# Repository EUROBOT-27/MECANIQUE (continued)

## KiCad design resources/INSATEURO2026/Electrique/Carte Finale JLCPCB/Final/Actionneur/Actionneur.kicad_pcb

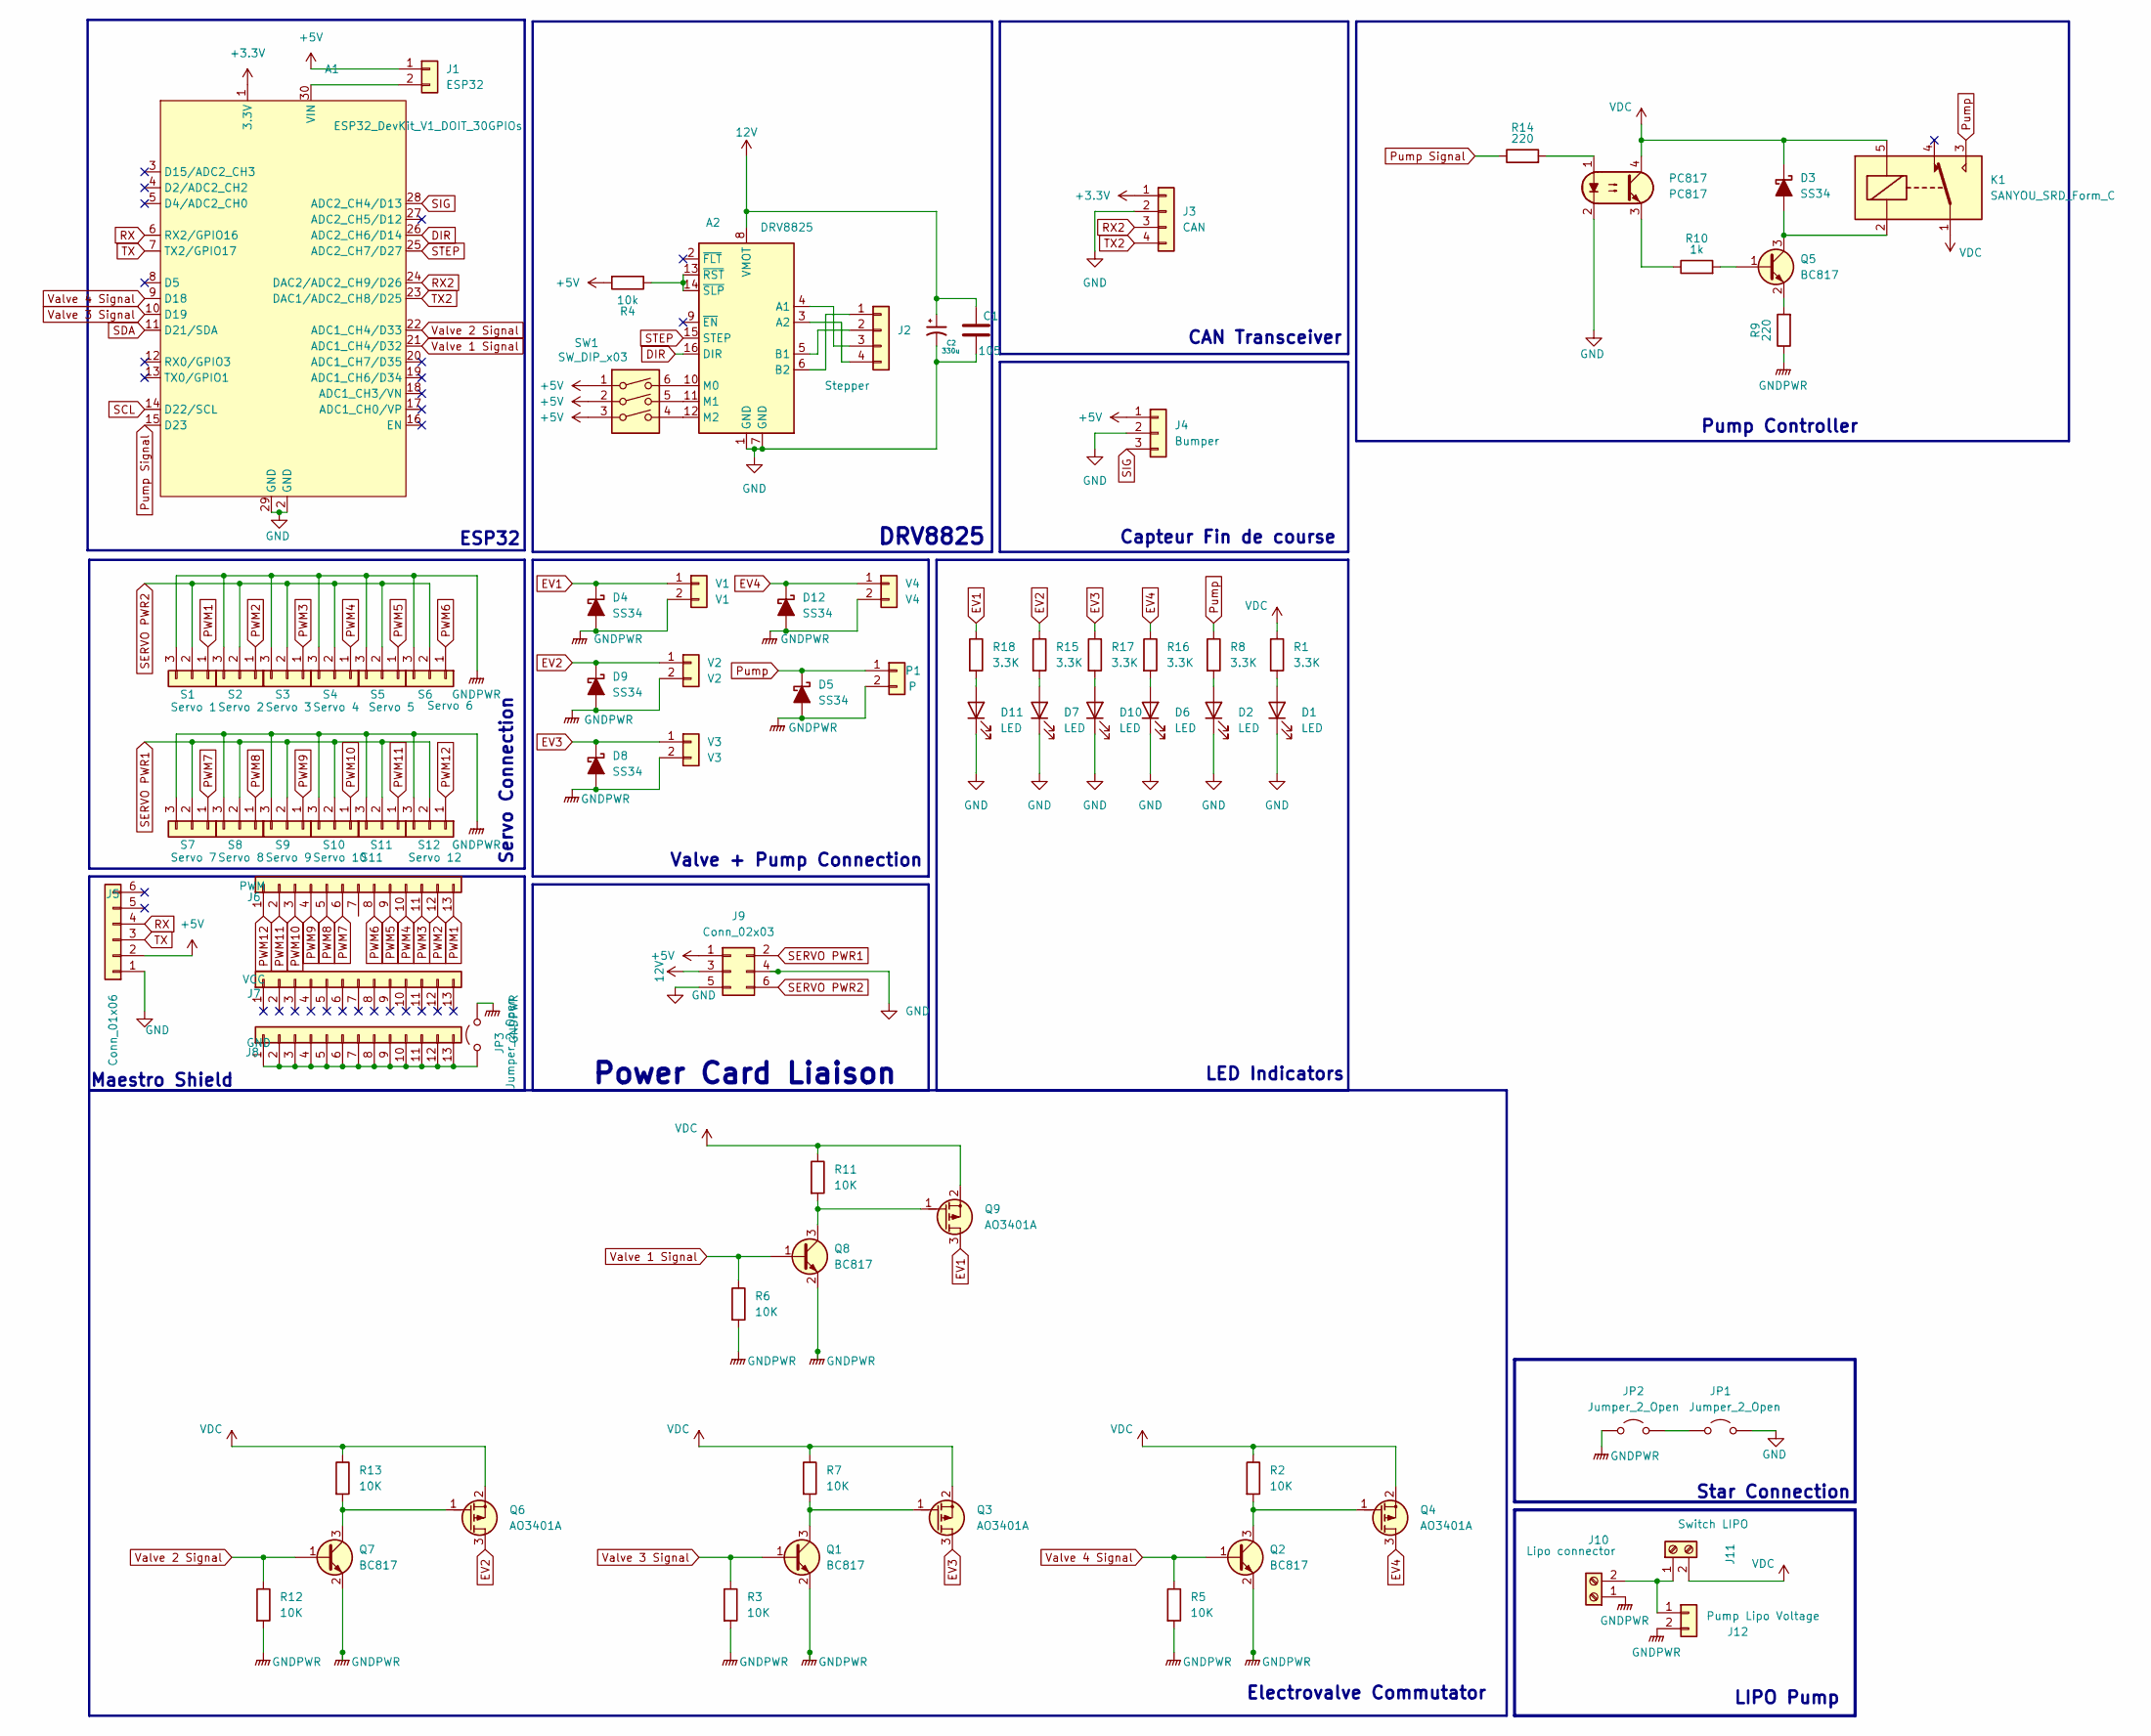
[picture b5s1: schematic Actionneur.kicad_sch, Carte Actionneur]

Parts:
A1: ESP32_DevKit_V1_DOIT_30GPIOs; DOIT_ESP32_DEVKIT_30Pins
A2: DRV8825; Pololu_Breakout-16_15.2x20.3mm
C1: 105; C_0603_1608Metric
C2: 330u; CP_Elec_10x10.5
D1, D2, D6, D7, D10, D11: LED; LED_0603_1608Metric
D3, D4, D5, D8, D9, D12: SS34; D_SOD-323
J1: ESP32; JST_XH_B2B-XH-A_1x02_P2.50mm_Vertical
J2: Stepper; JST_EH_B4B-EH-A_1x04_P2.50mm_Vertical
J3: CAN; JST_EH_B4B-EH-A_1x04_P2.50mm_Vertical
J4: Bumper; JST_EH_B3B-EH-A_1x03_P2.50mm_Vertical
J5: Conn_01x06; PinSocket_1x06_P2.54mm_Vertical
J6: PWM; PinSocket_1x13_P2.54mm_Vertical
J7: VCC; PinSocket_1x13_P2.54mm_Vertical
J8: GND; PinSocket_1x13_P2.54mm_Vertical
J9: Conn_02x03; Molex_Mini-Fit_Jr_5566-06A_2x03_P4.20mm_Vertical
J10: Lipo connector; TerminalBlock_Phoenix_MKDS-1,5-2-5.08_1x02_P5.08mm_Horizont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
J11: Switch LIPO; TerminalBlock_Phoenix_MKDS-1,5-2-5.08_1x02_P5.08mm_Horizont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
J12: Pump Lipo Voltage; JST_PH_B2B-PH-K_1x02_P2.00mm_Vertical
JP1, JP3: Jumper_2_Open; TestPoint_2Pads_Pitch2.54mm_Drill0.8mm
JP2: Jumper_2_Open; Jumper_P2.54mm_D0.7mm
K1: SANYOU_SRD_Form_C; Relay_SPDT_SANYOU_SRD_Series_Form_C
P1: P; JST_PH_B2B-PH-K_1x02_P2.00mm_Vertical
PC817: PC817; DIP-4_W7.62mm
Q1, Q2, Q5, Q7, Q8: BC817; SOT-23
Q3, Q4, Q6, Q9: AO3401A; SOT-23
R1, R8, R15, R16, R17, R18: 3.3K; R_0603_1608Metric
R2, R3, R5, R6, R7, R11, R12, R13: 10K; R_0603_1608Metric
R4: 10k; R_0603_1608Metric
R9, R14: 220; R_0603_1608Metric
R10: 1k; R_0603_1608Metric
S1: Servo 1; PinHeader_1x03_P2.54mm_Vertical
S2: Servo 2; PinHeader_1x03_P2.54mm_Vertical
S3: Servo 3; PinHeader_1x03_P2.54mm_Vertical
S4: Servo 4; PinHeader_1x03_P2.54mm_Vertical
S5: Servo 5; PinHeader_1x03_P2.54mm_Vertical
S6: Servo 6; PinHeader_1x03_P2.54mm_Vertical
S7: Servo 7; PinHeader_1x03_P2.54mm_Vertical
S8: Servo 8; PinHeader_1x03_P2.54mm_Vertical
S9: Servo 9; PinHeader_1x03_P2.54mm_Vertical
S10: Servo 10; PinHeader_1x03_P2.54mm_Vertical
S11: S11; PinHeader_1x03_P2.54mm_Vertical
S12: Servo 12; PinHeader_1x03_P2.54mm_Vertical
SW1: SW_DIP_x03; SW_DIP_SPSTx03_Slide_6.7x9.18mm_W6.73mm_P2.54mm_LowProfile_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
V1: V1; JST_PH_B2B-PH-K_1x02_P2.00mm_Vertical
V2: V2; JST_PH_B2B-PH-K_1x02_P2.00mm_Vertical
V3: V3; JST_PH_B2B-PH-K_1x02_P2.00mm_Vertical
V4: V4; JST_PH_B2B-PH-K_1x02_P2.00mm_Vertical

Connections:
12V: A2.8 (VMOT), C1.1, C2.1, J9.3
+3.3V: A1.1 (3.3V), J3.1
+5V: J1.1, J4.1, J5.2, J9.1, R4.2, SW1.1, SW1.2, SW1.3
DIR: A1.26 (ADC2_CH6/D14), A2.16 (DIR)
EV1: D4.1 (K), Q9.3 (D), R18.1, V1.1
EV2: D9.1 (K), Q6.3 (D), R15.1, V2.1
EV3: D8.1 (K), Q3.3 (D), R17.1, V3.1
EV4: D12.1 (K), Q4.3 (D), R16.1, V4.1
GND: A1.2 (GND), A1.29 (GND), A2.1 (GND), A2.7 (GND), C1.2, C2.2, D1.1 (K), D2.1 (K), D6.1 (K), D7.1 (K), D10.1 (K), D11.1 (K), J3.2, J4.2, J5.1, J9.4, J9.5, JP1.2 (B), PC817.2
GNDPWR: D4.2 (A), D5.2 (A), D8.2 (A), D9.2 (A), D12.2 (A), J10.1, J12.2, JP2.1 (A), JP3.2 (B), P1.2, Q1.2 (E), Q2.2 (E), Q7.2 (E), Q8.2 (E), R3.2, R5.2, R6.2, R9.1, R12.2, S1.3, S2.3, S3.3, S4.3, S5.3, S6.3, S7.3, S8.3, S9.3, S10.3, S11.3, S12.3, V1.2, V2.2, V3.2, V4.2
unnamed: A1.30 (VIN), J1.2
unnamed: A2.4 (A1), J2.3
unnamed: A2.3 (A2), J2.4
unnamed: A2.5 (B1), J2.2
unnamed: A2.6 (B2), J2.1
unnamed: A2.10 (M0), SW1.6
unnamed: A2.11 (M1), SW1.5
unnamed: A2.12 (M2), SW1.4
unnamed: A2.13 (~RST), A2.14 (~SLP), R4.1
unnamed: D1.2 (A), R1.2
unnamed: D2.2 (A), R8.2
unnamed: D3.2 (A), K1.2, Q5.3 (C)
unnamed: D6.2 (A), R16.2
unnamed: D7.2 (A), R15.2
unnamed: D10.2 (A), R17.2
unnamed: D11.2 (A), R18.2
unnamed: J8.1, J8.2, J8.3, J8.4, J8.5, J8.6, J8.7, J8.8, J8.9, J8.10, J8.11, J8.12, J8.13, JP3.1 (A)
unnamed: J10.2, J11.1, J12.1
unnamed: JP1.1 (A), JP2.2 (B)
unnamed: PC817.1, R14.2
unnamed: PC817.3, R10.1
unnamed: Q1.3 (C), Q3.1 (G), R7.2
unnamed: Q2.3 (C), Q4.1 (G), R2.2
unnamed: Q5.1 (B), R10.2
unnamed: Q5.2 (E), R9.2
unnamed: Q6.1 (G), Q7.3 (C), R13.2
unnamed: Q8.3 (C), Q9.1 (G), R11.2
PWM1: J6.13, S1.1
PWM2: J6.12, S2.1
PWM3: J6.11, S3.1
PWM4: J6.10, S4.1
PWM5: J6.9, S5.1
PWM6: J6.8, S6.1
PWM7: J6.6, S7.1
PWM8: J6.5, S8.1
PWM9: J6.4, S9.1
PWM10: J6.3, S10.1
PWM11: J6.2, S11.1
PWM12: J6.1, S12.1
Pump: D5.1 (K), K1.3, P1.1, R8.1
Pump Signal: A1.15 (D23), R14.1
RX: A1.6 (RX2/GPIO16), J5.4
RX2: A1.24 (DAC2/ADC2_CH9/D26), J3.3
SCL: A1.14 (D22/SCL)
SDA: A1.11 (D21/SDA)
SERVO PWR1: J9.2, S7.2, S8.2, S9.2, S10.2, S11.2, S12.2
SERVO PWR2: J9.6, S1.2, S2.2, S3.2, S4.2, S5.2, S6.2
SIG: A1.28 (ADC2_CH4/D13), J4.3
STEP: A1.25 (ADC2_CH7/D27), A2.15 (STEP)
TX: A1.7 (TX2/GPIO17), J5.3
TX2: A1.23 (DAC1/ADC2_CH8/D25), J3.4
VDC: D3.1 (K), J11.2, K1.1, K1.5, PC817.4, Q3.2 (S), Q4.2 (S), Q6.2 (S), Q9.2 (S), R1.1, R2.1, R7.1, R11.1, R13.1
Valve 1 Signal: A1.21 (ADC1_CH4/D32), Q8.1 (B), R6.1
Valve 2 Signal: A1.22 (ADC1_CH4/D33), Q7.1 (B), R12.1
Valve 3 Signal: A1.10 (D19), Q1.1 (B), R3.1
Valve 4 Signal: A1.9 (D18), Q2.1 (B), R5.1

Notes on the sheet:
LED Indicators
ESP32
LIPO Pump
Valve + Pump Connection
Star Connection
CAN Transceiver
Maestro Shield
Electrovalve Commutator
DRV8825
Pump Controller
Power Card Liaison
Servo Connection
Capteur Fin de course

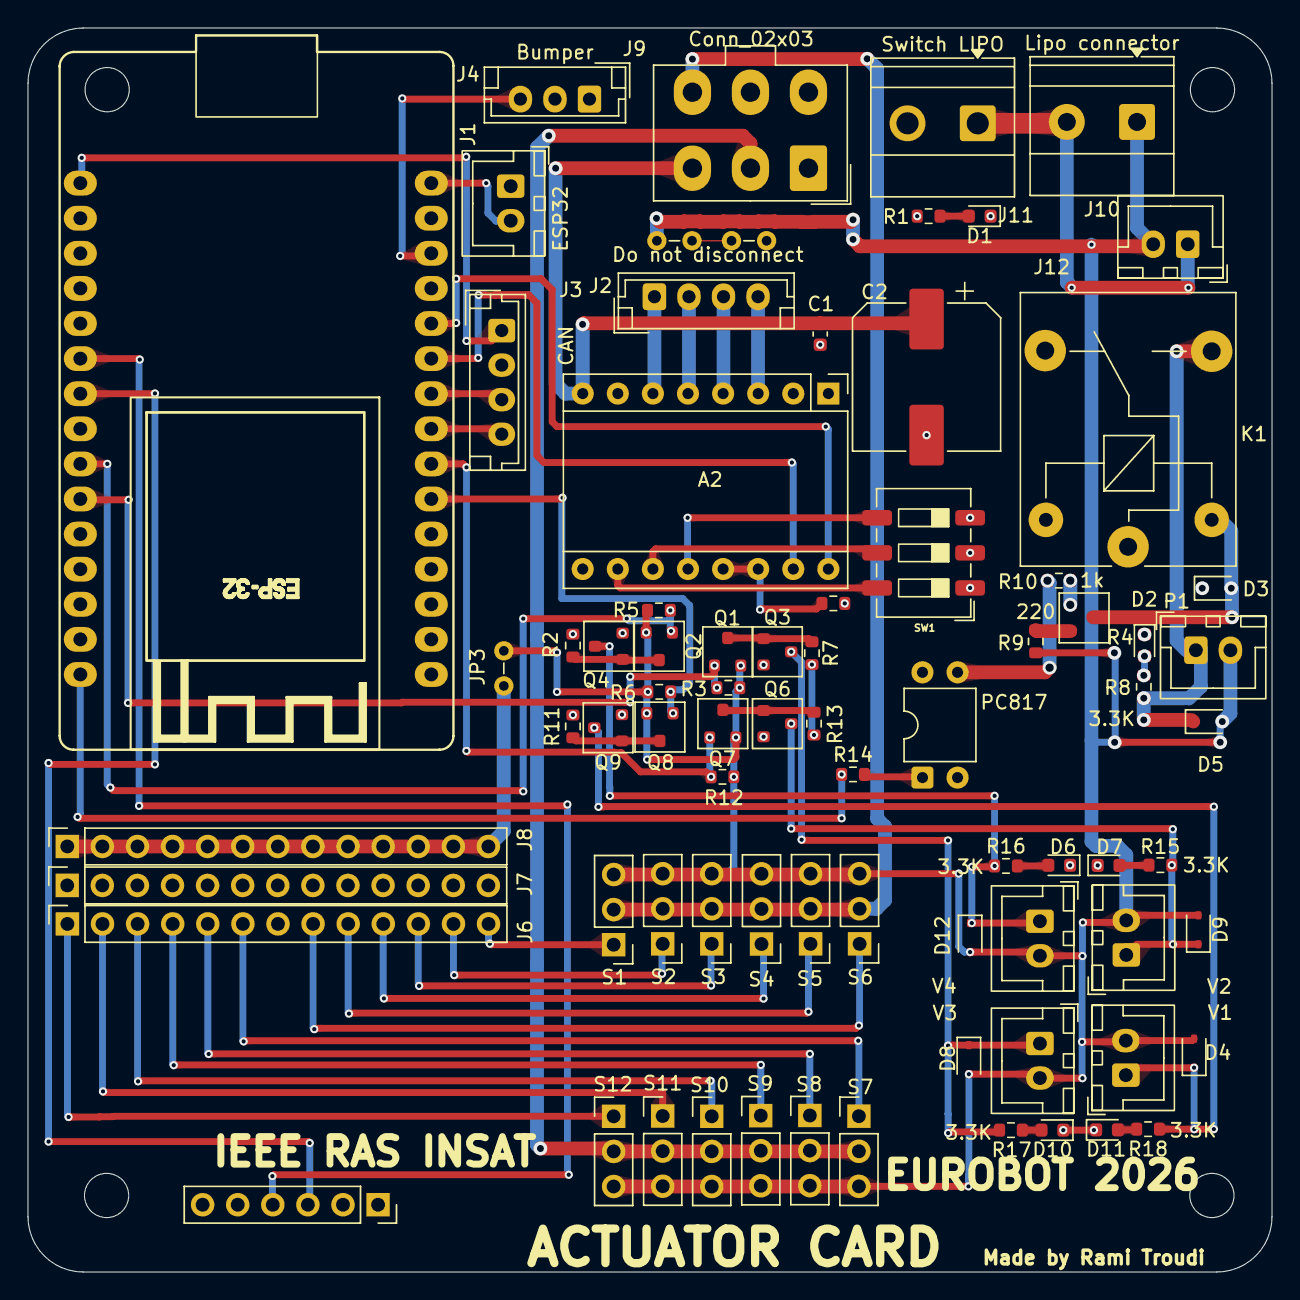
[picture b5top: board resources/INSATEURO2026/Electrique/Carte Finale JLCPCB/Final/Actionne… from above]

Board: 4 copper layers, 90.0 x 90.0 mm, 78 parts (0 on the bottom side), 64 nets.

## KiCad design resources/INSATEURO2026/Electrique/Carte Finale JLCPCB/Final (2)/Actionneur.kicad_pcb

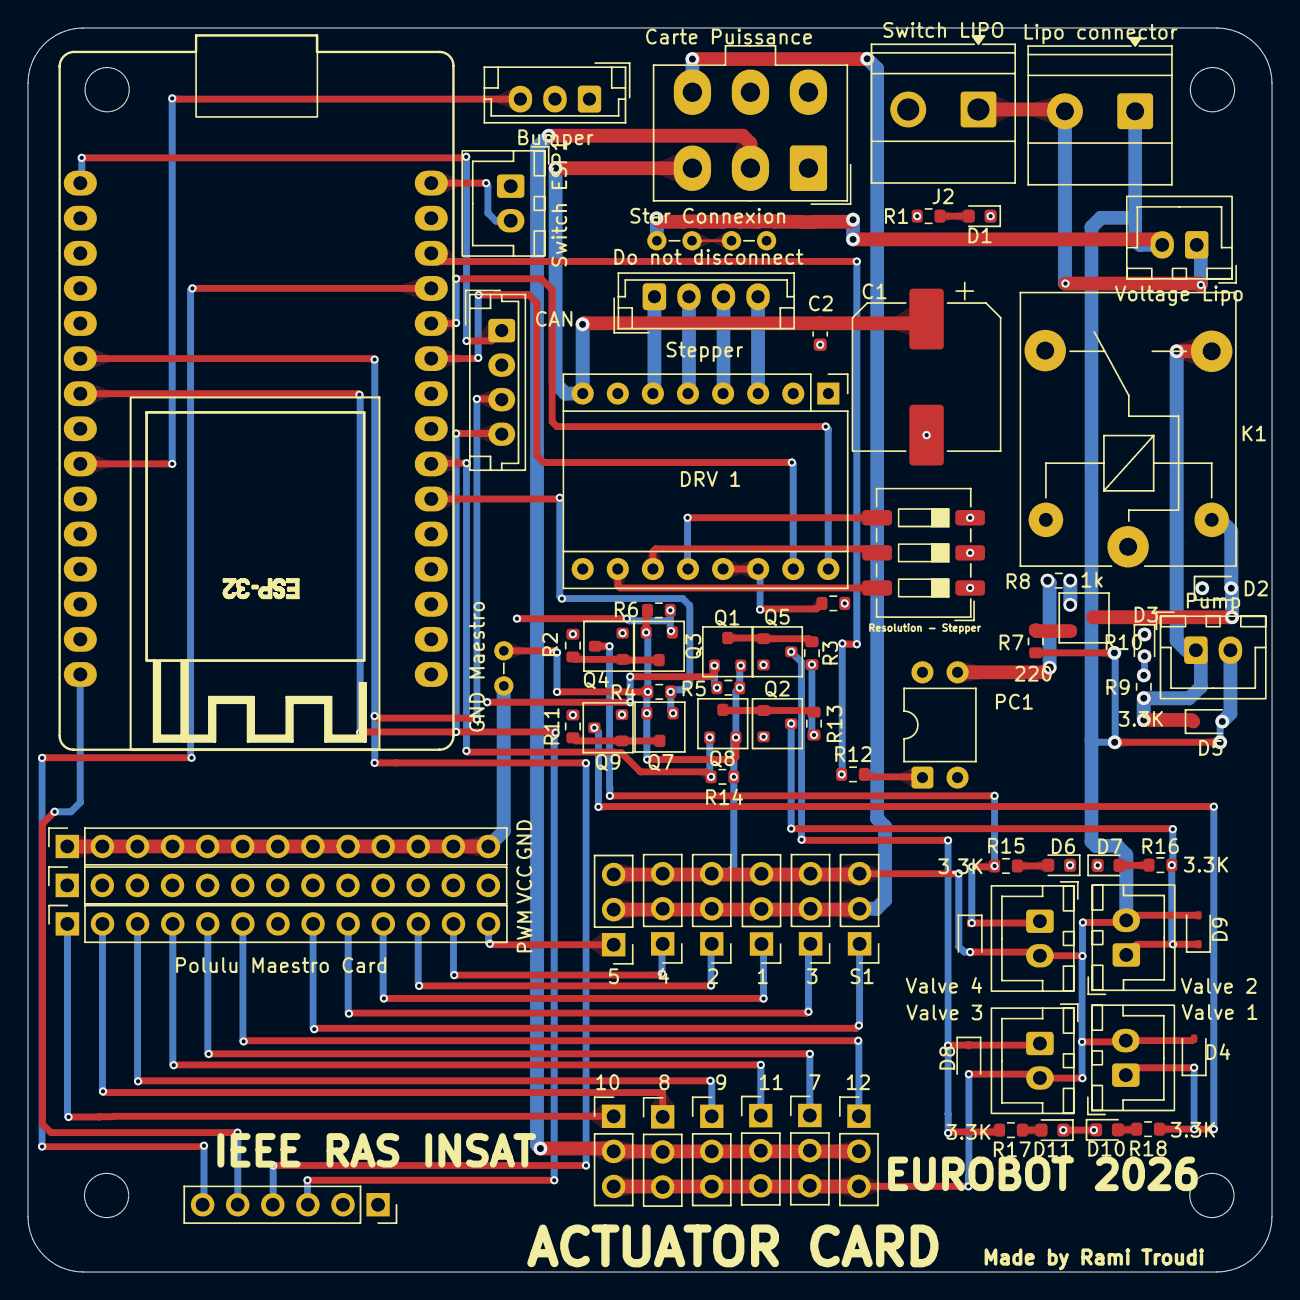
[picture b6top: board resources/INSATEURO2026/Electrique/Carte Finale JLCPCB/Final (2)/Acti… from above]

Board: 4 copper layers, 90.0 x 90.0 mm, 78 parts (0 on the bottom side), 64 nets.

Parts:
1: Servo 12; PinHeader_1x03_P2.54mm_Vertical
2: Servo 9; PinHeader_1x03_P2.54mm_Vertical
3: Servo 10; PinHeader_1x03_P2.54mm_Vertical
4: Servo 8; PinHeader_1x03_P2.54mm_Vertical
5: Servo 11; PinHeader_1x03_P2.54mm_Vertical
7: Servo 3; PinHeader_1x03_P2.54mm_Vertical
8: Servo 5; PinHeader_1x03_P2.54mm_Vertical
9: Servo 6; PinHeader_1x03_P2.54mm_Vertical
10: Servo 1; PinHeader_1x03_P2.54mm_Vertical
11: Servo 2; PinHeader_1x03_P2.54mm_Vertical
12: Servo 4; PinHeader_1x03_P2.54mm_Vertical
A1: ESP32_DevKit_V1_DOIT_30GPIOs; DOIT_ESP32_DEVKIT_30Pins
Bumper: Conn_01x03; JST_EH_B3B-EH-A_1x03_P2.50mm_Vertical
C1: 1000u; CP_Elec_10x10.5
C2: 105; C_0603_1608Metric
CAN: Conn_01x04; JST_EH_B4B-EH-A_1x04_P2.50mm_Vertical
Carte Puissance: Conn_02x03; Molex_Mini-Fit_Jr_5566-06A_2x03_P4.20mm_Vertical
D1, D3, D6, D7, D10, D11: LED; LED_0603_1608Metric
D2, D4, D5, D8, D9: SS34; D_SOD-323
DRV 1: Pololu_Breakout_DRV8825; Pololu_Breakout-16_15.2x20.3mm
GND: GND; PinSocket_1x13_P2.54mm_Vertical
GND Maestro: Jumper_2_Open; Jumper_P2.54mm_D0.7mm
J1: Lipo connector; TerminalBlock_Phoenix_MKDS-1,5-2-5.08_1x02_P5.08mm_Horizont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
J2: Switch LIPO; TerminalBlock_Phoenix_MKDS-1,5-2-5.08_1x02_P5.08mm_Horizont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
J3: Conn_01x06; PinSocket_1x06_P2.54mm_Vertical
JP1: Jumper_2_Open; Jumper_P2.54mm_D0.7mm
K1: SANYOU_SRD_Form_C; Relay_SPDT_SANYOU_SRD_Series_Form_C
PC1: PC817; DIP-4_W7.62mm
PWM: PWM; PinSocket_1x13_P2.54mm_Vertical
Polulu Maestro Card: SS34; D_SOD-323
Pump: V1; JST_XH_B2B-XH-A_1x02_P2.50mm_Vertical
Q1, Q3, Q6, Q7, Q8: BC817; SOT-23
Q2, Q4, Q5, Q9: AO3401A; SOT-23
R1, R9, R15, R16, R17, R18: 3.3K; R_0603_1608Metric
R2, R3, R4, R5, R6, R11, R13, R14: 10K; R_0603_1608Metric
R7, R12: 220; R_0603_1608Metric
R8: 1k; R_0603_1608Metric
R10: 10k; R_0603_1608Metric
Resolution - Stepper: SW_DIP_x03; SW_DIP_SPSTx03_Slide_6.7x9.18mm_W6.73mm_P2.54mm_LowProfile_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
S1: Servo 1; PinHeader_1x03_P2.54mm_Vertical
Star Connexion: Jumper_2_Open; Jumper_P2.54mm_D0.7mm
Stepper: Stepper connector; JST_EH_B4B-EH-A_1x04_P2.50mm_Vertical
Switch ESP1: V1; JST_XH_B2B-XH-A_1x02_P2.50mm_Vertical
VCC: VCC; PinSocket_1x13_P2.54mm_Vertical
Valve 1, Valve 2, Valve 3, Valve 4: V1; JST_XH_B2B-XH-A_1x02_P2.50mm_Vertical
Voltage Lipo: Pump Lipo Voltage; JST_XH_B2B-XH-A_1x02_P2.50mm_Vertical

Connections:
12V: C1.1, C2.1, Carte Puissance.3, DRV 1.8 (VMOT)
+3.3V: A1.1 (3.3V), CAN.1
+5V: Bumper.1, Carte Puissance.1, J3.2, R10.2, Resolution - Stepper.1, Resolution - Stepper.2, Resolution - Stepper.3
DIR: A1.26 (ADC2_CH6/D14), DRV 1.16 (DIR)
ERR: A1.27 (ADC2_CH5/D12), J3.6
EV1: D4.1 (K), Q9.3 (D), R18.1, Valve 1.1
EV2: D9.1 (K), Q2.3 (D), R16.1, Valve 2.1
EV3: D8.1 (K), Q5.3 (D), R17.1, Valve 3.1
EV4: Polulu Maestro Card.1 (K), Q4.3 (D), R15.1, Valve 4.1
GND: A1.2 (GND), A1.29 (GND), Bumper.2, C1.2, C2.2, CAN.2, Carte Puissance.4, Carte Puissance.5, D1.1 (K), D3.1 (K), D6.1 (K), D7.1 (K), D10.1 (K), D11.1 (K), DRV 1.1 (GND), DRV 1.7 (GND), J3.1, PC1.2, Star Connexion.2 (B)
GNDPWR: 1.3, 2.3, 3.3, 4.3, 5.3, 7.3, 8.3, 9.3, 10.3, 11.3, 12.3, D4.2 (A), D5.2 (A), D8.2 (A), D9.2 (A), GND Maestro.2 (B), J1.1, JP1.1 (A), Polulu Maestro Card.2 (A), Pump.2, Q1.2 (E), Q3.2 (E), Q7.2 (E), Q8.2 (E), R4.2, R5.2, R6.2, R7.1, R14.2, S1.3, Valve 1.2, Valve 2.2, Valve 3.2, Valve 4.2, Voltage Lipo.2
unnamed: A1.30 (VIN), Switch ESP1.2
unnamed: DRV 1.4 (A1), Stepper.3
unnamed: DRV 1.3 (A2), Stepper.4
unnamed: DRV 1.5 (B1), Stepper.2
unnamed: DRV 1.6 (B2), Stepper.1
unnamed: DRV 1.10 (M0), Resolution - Stepper.6
unnamed: DRV 1.11 (M1), Resolution - Stepper.5
unnamed: DRV 1.12 (M2), Resolution - Stepper.4
unnamed: DRV 1.13 (~RST), DRV 1.14 (~SLP), R10.1
unnamed: D2.2 (A), K1.2, Q6.3 (C)
unnamed: D10.2 (A), R18.2
unnamed: D7.2 (A), R16.2
unnamed: D11.2 (A), R17.2
unnamed: D6.2 (A), R15.2
unnamed: D3.2 (A), R9.2
unnamed: D1.2 (A), R1.2
unnamed: GND.1, GND.2, GND.3, GND.4, GND.5, GND.6, GND.7, GND.8, GND.9, GND.10, GND.11, GND.12, GND.13, GND Maestro.1 (A)
unnamed: J1.J27 (Pin_2), J2.1, Voltage Lipo.1
unnamed: JP1.2 (B), Star Connexion.1 (A)
unnamed: PC1.1, R12.2
unnamed: PC1.3, R8.1
unnamed: Q2.1 (G), Q8.3 (C), R13.2
unnamed: Q1.3 (C), Q5.1 (G), R3.2
unnamed: Q7.3 (C), Q9.1 (G), R11.2
unnamed: Q3.3 (C), Q4.1 (G), R2.2
unnamed: Q6.1 (B), R8.2
unnamed: Q6.2 (E), R7.2
PWM1: PWM.13, S1.1
PWM2: 4.1, PWM.12
PWM3: 2.1, PWM.11
PWM4: 3.1, PWM.10
PWM5: 5.1, PWM.9
PWM6: 1.1, PWM.8
PWM7: 10.1, PWM.6
PWM8: 11.1, PWM.5
PWM9: 7.1, PWM.4
PWM10: 12.1, PWM.3
PWM11: 8.1, PWM.2
PWM12: 9.1, PWM.1
Pump: D5.1 (K), K1.3, Pump.1, R9.1
Pump Signal: A1.28 (ADC2_CH4/D13), R12.1
RST: A1.15 (D23), J3.5
RX: A1.6 (RX2/GPIO16), CAN.3, J3.4
SERVO PWR1: 7.2, 8.2, 9.2, 10.2, 11.2, 12.2, Carte Puissance.2
SERVO PWR2: 1.2, 2.2, 3.2, 4.2, 5.2, Carte Puissance.6, S1.2
SIG: A1.9 (D18), Bumper.3
STEP: A1.25 (ADC2_CH7/D27), DRV 1.15 (STEP)
TX: A1.7 (TX2/GPIO17), CAN.4, J3.3
VDC: D2.1 (K), J2.2, K1.1, K1.5, PC1.4, Q2.2 (S), Q4.2 (S), Q5.2 (S), Q9.2 (S), R1.1, R2.1, R3.1, R11.1, R13.1
Valve 1 Signal: A1.21 (ADC1_CH4/D32), Q7.1 (B), R4.1
Valve 2 Signal: A1.22 (ADC1_CH4/D33), Q8.1 (B), R14.1
Valve 3 Signal: A1.23 (DAC1/ADC2_CH8/D25), Q1.1 (B), R5.1
Valve 4 Signal: A1.24 (DAC2/ADC2_CH9/D26), Q3.1 (B), R6.1

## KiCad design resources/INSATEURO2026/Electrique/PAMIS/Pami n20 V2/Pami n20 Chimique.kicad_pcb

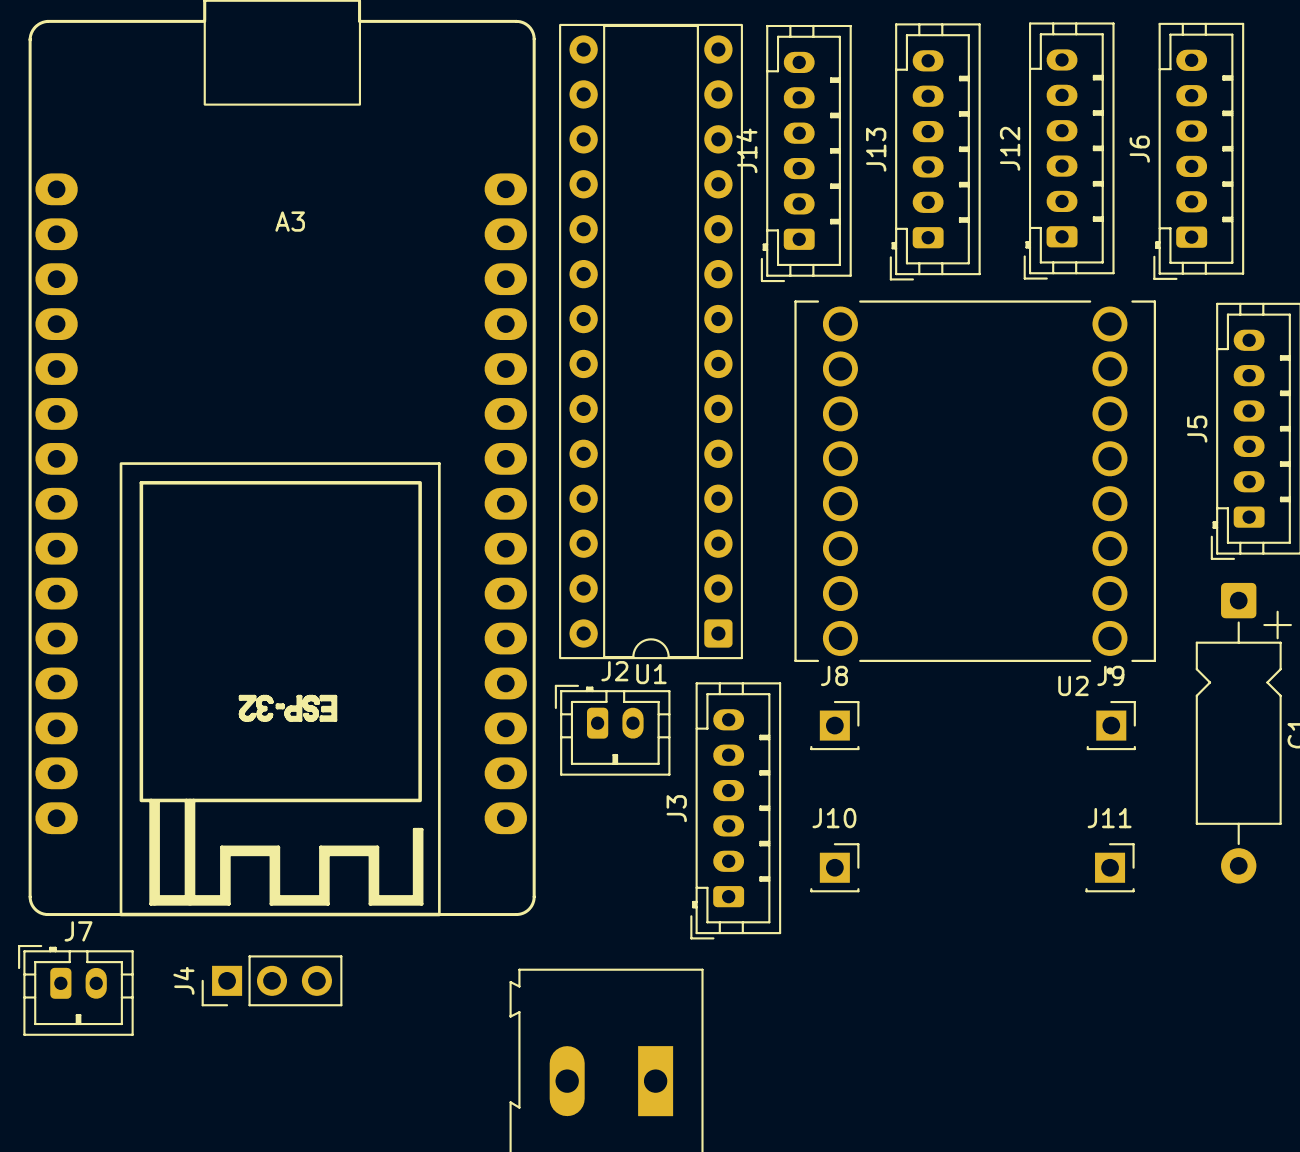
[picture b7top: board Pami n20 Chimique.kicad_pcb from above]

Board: 2 copper layers, 18 parts (0 on the bottom side), 31 nets, no tracks yet.

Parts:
A3: ESP32_DevKit_V1_DOIT_30GPIOs; DOIT_ESP32_DEVKIT_30Pins
C1: C_Polarized; CP_Axial_L10.0mm_D4.5mm_P15.00mm_Horizontal
J1: Screw_Terminal_01x02; TerminalBlock_Altech_AK300-2_P5.00mm
J2: URG; JST_PH_B2B-PH-K_1x02_P2.00mm_Vertical
J3: ENC2; JST_PH_B6B-PH-K_1x06_P2.00mm_Vertical
J4: Servo Connector; PinHeader_1x03_P2.54mm_Vertical
J5: ENC1; JST_PH_B6B-PH-K_1x06_P2.00mm_Vertical
J6: TOF1; JST_PH_B6B-PH-K_1x06_P2.00mm_Vertical
J7: Jack; JST_PH_B2B-PH-K_1x02_P2.00mm_Vertical
J8, J9, J10, J11: PINHD_1x1_Female; PinSocket_1x01_P2.54mm_Vertical
J12: TOF2; JST_PH_B6B-PH-K_1x06_P2.00mm_Vertical
J13: TOF3; JST_PH_B6B-PH-K_1x06_P2.00mm_Vertical
J14: TOF4; JST_PH_B6B-PH-K_1x06_P2.00mm_Vertical
U1: MCP23017_SP; DIP-28_W7.62mm_Socket
U2: ROB-14450; MODULE_ROB-14450

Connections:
+3.3V: A3.1 (3.3V), C1.1, J6.3, J12.3, J13.3, J14.3, U1.9 (VDD), U2.2 (VCC)
+5V: A3.30 (VIN), J3.2, J4.2, J5.2, J9.1, U2.1 (VM), U2.13 (STBY)
A1: J5.1, U2.4 (A01)
A2: J5.6, U2.5 (A02)
B1: J3.1, U2.7 (B01)
B2: J3.6, U2.6 (B02)
ENC1_A: A3.22 (ADC1_CH4/D33), J5.4
ENC1_B: A3.21 (ADC1_CH4/D32), J5.3
ENC2_A: A3.20 (ADC1_CH7/D35), J3.4
ENC2_B: A3.19 (ADC1_CH6/D34), J3.3
GND: A3.2 (GND), C1.2, J1.1, J3.5, J4.3, J5.5, J6.4, J7.2, J10.1, J11.1, J12.4, J13.4, J14.4, U1.10 (VSS), U1.15 (A0), U1.16 (A1), U1.17 (A2), U2.3 (GND), U2.8 (GND), U2.9 (GND)
GPIO1: J6.2, U1.1 (GPB0)
GPIO2: J12.2, U1.2 (GPB1)
GPIO3: J13.2, U1.3 (GPB2)
GPIO4: J14.2, U1.4 (GPB3)
JACK: A3.15 (D23), J7.1
M1_PWM: A3.8 (D5), U2.16 (PWMA)
M2_PWM: A3.27 (ADC2_CH5/D12), U2.10 (PWMB)
MOT_AIN1: U1.27 (GPA6), U2.14 (AI1)
MOT_AIN2: U1.28 (GPA7), U2.15 (AI2)
MOT_BIN1: U1.26 (GPA5), U2.12 (BI1)
MOT_BIN2: U1.25 (GPA4), U2.11 (BI2)
unnamed: J1.2, J2.1
SCL: A3.14 (D22/SCL), J6.5, J12.5, J13.5, J14.5, U1.12 (SCK)
SDA: A3.11 (D21/SDA), J6.6, J12.6, J13.6, J14.6, U1.13 (SDA)
SERVO_PWM: A3.9 (D18), J4.1
Supply: J2.2, J8.1
XShunt1: J6.1, U1.24 (GPA3)
XShunt2: J12.1, U1.23 (GPA2)
XShunt3: J13.1, U1.22 (GPA1)
XShunt4: J14.1, U1.21 (GPA0)

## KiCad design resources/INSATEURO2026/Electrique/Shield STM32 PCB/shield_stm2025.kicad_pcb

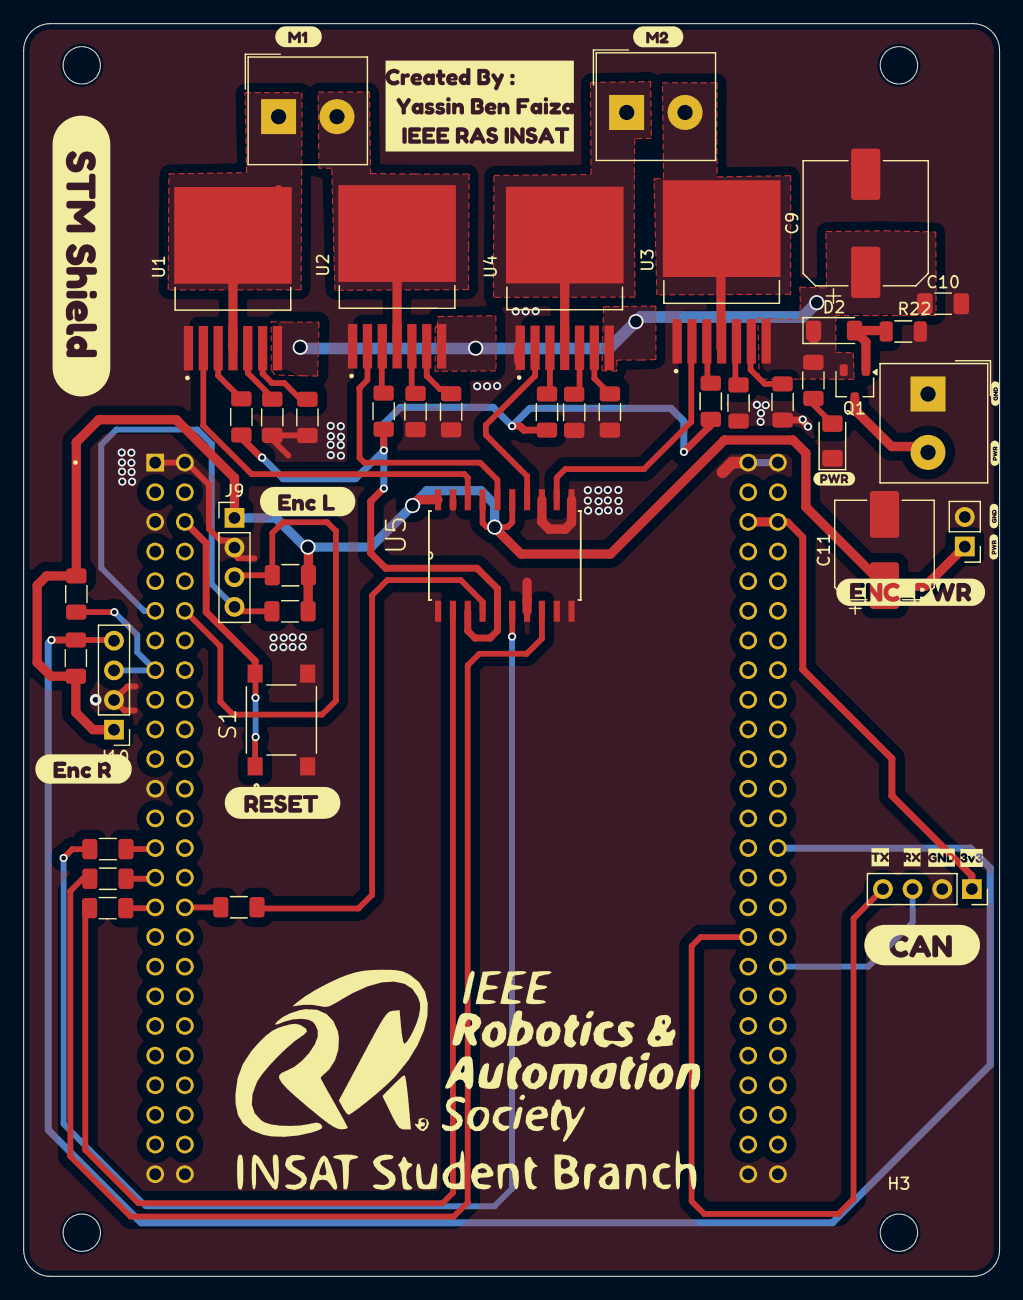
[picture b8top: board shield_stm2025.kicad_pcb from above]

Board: 2 copper layers, 83.6 x 107.3 mm, 64 parts (0 on the bottom side), 43 nets.

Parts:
C9: 470u; CP_Elec_10x10.5
C10: 100n; C_1206_3216Metric_Pad1.33x1.80mm_HandSolder
C11: 10u; CP_Elec_8x5.4
D1: LED; LED_1206_3216Metric_Pad1.42x1.75mm_HandSolder
D2: BZV55B10; D_MiniMELF
H1, H2, H3, H4: MountingHole; MountingHole_3.2mm_M3
J2: OUT M1; Altech_AK100_1x02_P5.00mm
J3: OUT M2; Altech_AK100_1x02_P5.00mm
J4: 24V input; Altech_AK100_1x02_P5.00mm
J6: CAN; PinSocket_1x04_P2.54mm_Vertical
J8: Alimentation; PinHeader_1x02_P2.54mm_Vertical
J9: Encoder_Left; PinHeader_1x04_P2.54mm_Vertical
J10: Encoder_Right; PinHeader_1x04_P2.54mm_Vertical
Q1: AO3401A; SOT-23W
R1, R2, R5, R6, R9, R10, R15, R16: 10K; R_1206_3216Metric_Pad1.30x1.75mm_HandSolder
R3, R4, R7, R8, R11, R12, R13, R14: 4.7K; R_1206_3216Metric_Pad1.30x1.75mm_HandSolder
R17, R18, R19, R20, R21: R; R_1206_3216Metric_Pad1.30x1.75mm_HandSolder
R22: 10K; R_1206_3216Metric
S1: PTS645SK50SMTR92LFS; SW_PTS645SK50SMTR92LFS
TB1: STM32F4DISCOVERY; MODULE_STM32F407G-DISC1
U1, U2, U3, U4: BTS7960B; DPAK127P1490X440-8N
U5: 74HC244; SOIC127P1032X265-20N
kibuzzard-6821E684: G***; kibuzzard-6821E684
kibuzzard-6821EA5D: G***; kibuzzard-6821EA5D
kibuzzard-6821EA78: G***; kibuzzard-6821EA78
kibuzzard-6821EB0D: G***; kibuzzard-6821EB0D
kibuzzard-6821EB1E: G***; kibuzzard-6821EB1E
kibuzzard-6821EB6B: G***; kibuzzard-6821EB6B
kibuzzard-6821FFFF: G***; kibuzzard-6821FFFF
kibuzzard-6824CA9A, kibuzzard-6824CA9A#2: G***; kibuzzard-6824CA9A
kibuzzard-6824CA75, kibuzzard-6824CA75#2: G***; kibuzzard-6824CA75
kibuzzard-6824CD1D: G***; kibuzzard-6824CD1D
kibuzzard-6824CD32: G***; kibuzzard-6824CD32
kibuzzard-6824CD49: G***; kibuzzard-6824CD49
kibuzzard-6824CD70: G***; kibuzzard-6824CD70
kibuzzard-6881FAE2: G***; kibuzzard-6881FAE2
kibuzzard-68220201: G***; kibuzzard-68220201
kibuzzard-68220375: G***; kibuzzard-68220375

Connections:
+3.3V: J6.1, TB1.P2_5 (3V), TB1.P2_6 (3V)
EN: R2.1, R6.1, R10.2, R15.2, U5.3 (2Y0), U5.5 (2Y1)
GND: C9.2, C10.2, C11.2, D1.1 (K), J4.1, J6.2, J8.2, J9.2, J10.2, R3.1, R4.2, R7.1, R8.2, R11.1, R12.2, R13.2, R14.1, R22.2, S1.3, S1.4, TB1.P1_1 (GND), TB1.P1_2 (GND), TB1.P1_5 (GND), TB1.P1_23 (GND), TB1.P1_49 (GND), TB1.P1_50 (GND), TB1.P2_1 (GND), TB1.P2_2 (GND), TB1.P2_49 (GND), TB1.P2_50 (GND), U1.1 (GND), U2.1 (GND), U3.1 (GND), U4.1 (GND), U5.1 (1OE), U5.7 (2Y2), U5.9 (2Y3), U5.10 (GND), U5.11 (2A3), U5.13 (2A2), U5.19 (2OE)
LPWM1: R1.1, TB1.P1_32 (PE14)
LPWM2: R16.1, TB1.P1_29 (PE11)
NRST: S1.1, S1.2, TB1.P1_6 (NRST)
unnamed: D1.2 (A), R17.2
unnamed: D2.2 (A), Q1.1 (G), R22.1
unnamed: J2.1, U1.4 (OUT), U1.8 (OUT)
unnamed: J2.2, U2.4 (OUT), U2.8 (OUT)
unnamed: J3.1, U4.4 (OUT), U4.8 (OUT)
unnamed: J3.2, U3.4 (OUT), U3.8 (OUT)
unnamed: J4.2, Q1.3 (D)
unnamed: R2.2, U1.3 (INH)
unnamed: R4.1, U1.6 (IS)
unnamed: R3.2, U1.5 (SR)
unnamed: R15.1, U2.3 (INH)
unnamed: R8.1, U2.6 (IS)
unnamed: R7.2, U2.5 (SR)
unnamed: R10.1, U3.3 (INH)
unnamed: R13.1, U3.6 (IS)
unnamed: R11.2, U3.5 (SR)
unnamed: R6.2, U4.3 (INH)
unnamed: R12.1, U4.6 (IS)
unnamed: R14.2, U4.5 (SR)
unnamed: R9.2, U5.2 (1A0)
unnamed: R1.2, U5.4 (1A1)
unnamed: R5.2, U5.6 (1A2)
unnamed: R16.2, U5.8 (1A3)
OUT1: U1.2 (IN), U5.18 (1Y0)
OUT2: U2.2 (IN), U5.16 (1Y1)
OUT3: U4.2 (IN), U5.14 (1Y2)
OUT4: U3.2 (IN), U5.12 (1Y3)
PA0: J9.3, R20.1, TB1.P1_12 (PA0-WKUP)
PA1: J9.4, R21.1, TB1.P1_11 (PA1)
PA5: J10.3, R18.1, TB1.P1_15 (PA5)
PB3: J10.4, R19.1, TB1.P2_28 (PB3)
RPWM1: R9.1, TB1.P1_31 (PE13)
RPWM2: R5.1, TB1.P1_27 (PE9)
RX: J6.3, TB1.P2_36 (PD0)
Supply: C9.1, C10.1, D2.1 (K), Q1.2 (S), R17.1, U1.7 (VS), U2.7 (VS), U3.7 (VS), U4.7 (VS)
TX: J6.4, TB1.P2_33 (PD1)
VCC: C11.1, J8.1, J9.1, J10.1, R18.2, R19.2, R20.2, R21.2, U5.15 (2A1), U5.17 (2A0), U5.20 (VCC)

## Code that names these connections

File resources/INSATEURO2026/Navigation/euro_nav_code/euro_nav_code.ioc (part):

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Mcu.Name=STM32F407V(E-G)Tx
Mcu.Package=LQFP100
Mcu.UserName=STM32F407VGTx
PA0-WKUP.Signal=S_TIM5_CH1
PA1.Signal=S_TIM5_CH2
PA5.Signal=S_TIM2_CH1_ETR
PB3.Signal=S_TIM2_CH2
PD0.Mode=CAN_Activate
PD0.Signal=CAN1_RX
PD1.Mode=CAN_Activate
PD1.Signal=CAN1_TX
PE11.Signal=S_TIM1_CH2
PE13.Signal=S_TIM1_CH3
PE14.Signal=S_TIM1_CH4
PE9.Signal=S_TIM1_CH1
PH0-OSC_IN.Mode=HSE-External-Oscillator
PH0-OSC_IN.Signal=RCC_OSC_IN
PH1-OSC_OUT.Mode=HSE-External-Oscillator
PH1-OSC_OUT.Signal=RCC_OSC_OUT
RCC.HSE_VALUE=8000000
RCC.SYSCLKFreq_VALUE=168000000
RCC.SYSCLKSource=RCC_SYSCLKSOURCE_PLLCLK
board=STM32F407G-DISC1
boardIOC=true
